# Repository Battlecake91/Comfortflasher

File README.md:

Firmware and PCB files for Comfortflasher Module for Mazda / Ford and some BMWs

From: https://mazda626ge.de/viewtopic.php?f=31&t=6114

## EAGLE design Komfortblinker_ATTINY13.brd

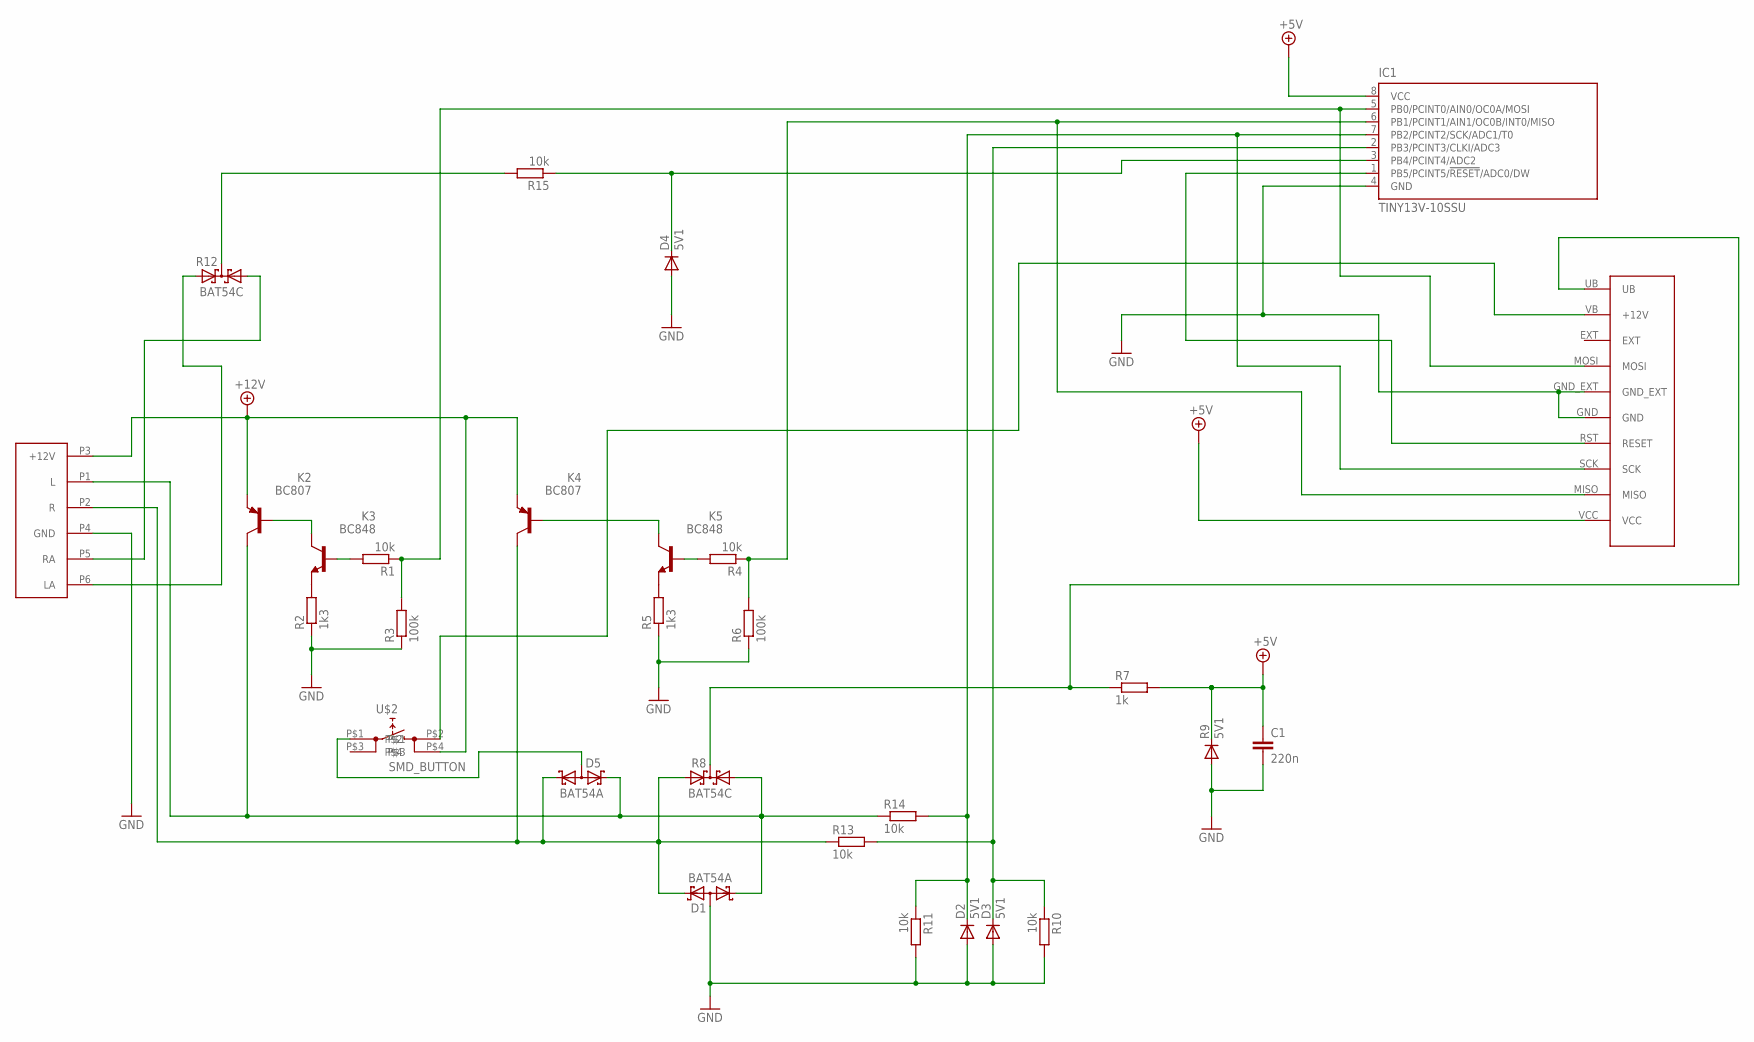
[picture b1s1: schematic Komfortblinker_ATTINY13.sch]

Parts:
C1: 220n; C0805
D1, D5: BAT54A; SOT23
D2, D3, D4: 5V1; SOD123
IC1: TINY13V-10SSU; 8S1
K2, K4: BC807; SOT23-BEC
K3, K5: BC848; SOT23
R1, R4, R10, R11, R15: 10k; R0805
R2, R5: 1k3; R0805
R3, R6: 100k; R0805
R7: 1k; M0805
R8, R12: BAT54C; SOT23
R9: 5V1; MINIMELF
R13, R14: 10k; M0805
U$2: SMD_BUTTON
U$3: PROGRAMMING
U$4: CON-KOMFORT

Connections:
+5V: C1.1, IC1.8 (VCC), R7.2, R9.C, U$3.VCC
+12V: K2.E, K4.E, U$2.P$4, U$4.P3 (+12V)
+12V2: U$2.P$2, U$3.VB (+12V)
BK2: K2.B, K3.3 (C)
BK3: K3.1 (B), R1.2
BK4: K4.B, K5.3 (C)
BK5: K5.1 (B), R4.2
FB: D4.C, IC1.3 (PB4/PCINT4/ADC2), R15.1
GND: C1.2, D1.3 (AA), D2.A, D3.A, D4.A, IC1.4 (GND), R2.1, R3.1, R5.1, R6.1, R9.A, R10.2, R11.2, U$3.GND, U$3.GND_EXT, U$4.P4 (GND)
L: D1.1 (K1), D5.2 (K2), K2.C, R8.1 (A1), R14.1, U$4.P1 (L)
L2: D2.C, IC1.7 (PB2/PCINT2/SCK/ADC1/T0), R11.1, R14.2, U$3.SCK
LA: R12.2 (A2), U$4.P6 (LA)
LRA: R12.3 (CC), R15.2
LS: IC1.5 (PB0/PCINT0/AIN0/OC0A/MOSI), R1.1, R3.2, U$3.MOSI
unnamed: K5.2 (E), R5.2
unnamed: K3.2 (E), R2.2
unnamed: D5.3 (AA), U$2.P$1
R: D1.2 (K2), D5.1 (K1), K4.C, R8.2 (A2), R13.1, U$4.P2 (R)
R2: D3.C, IC1.2 (PB3/PCINT3/CLKI/ADC3), R10.1, R13.2
RA: R12.1 (A1), U$4.P5 (RA)
RESET: IC1.1 (PB5/PCINT5/!RESET!/ADC0/DW), U$3.RST (RESET)
RS: IC1.6 (PB1/PCINT1/AIN1/OC0B/INT0/MISO), R4.1, R6.2, U$3.MISO
UB: R7.1, R8.3 (CC), U$3.UB

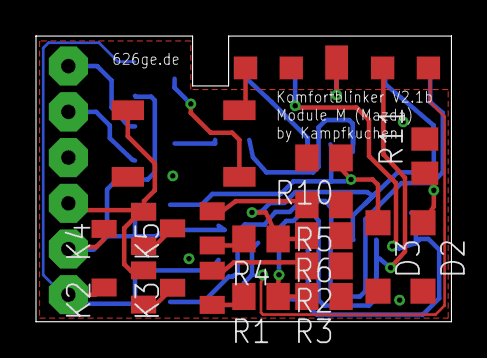
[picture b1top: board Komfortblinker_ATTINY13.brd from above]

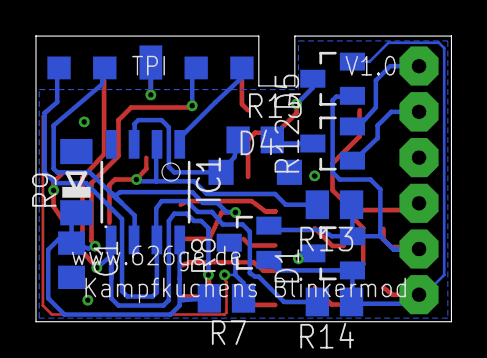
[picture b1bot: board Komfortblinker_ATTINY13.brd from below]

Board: 2 copper layers, 23.1 x 15.9 mm, 29 parts (12 on the bottom side), 23 nets.

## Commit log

2024-12-23 Update main.c
    Changed many stuff
    Added Feedback-Timeout
    Changed Min-Time to 100ms
    added initial cycle-setup
    changed many variablenames
2024-12-23 Added Debug and Release files.
